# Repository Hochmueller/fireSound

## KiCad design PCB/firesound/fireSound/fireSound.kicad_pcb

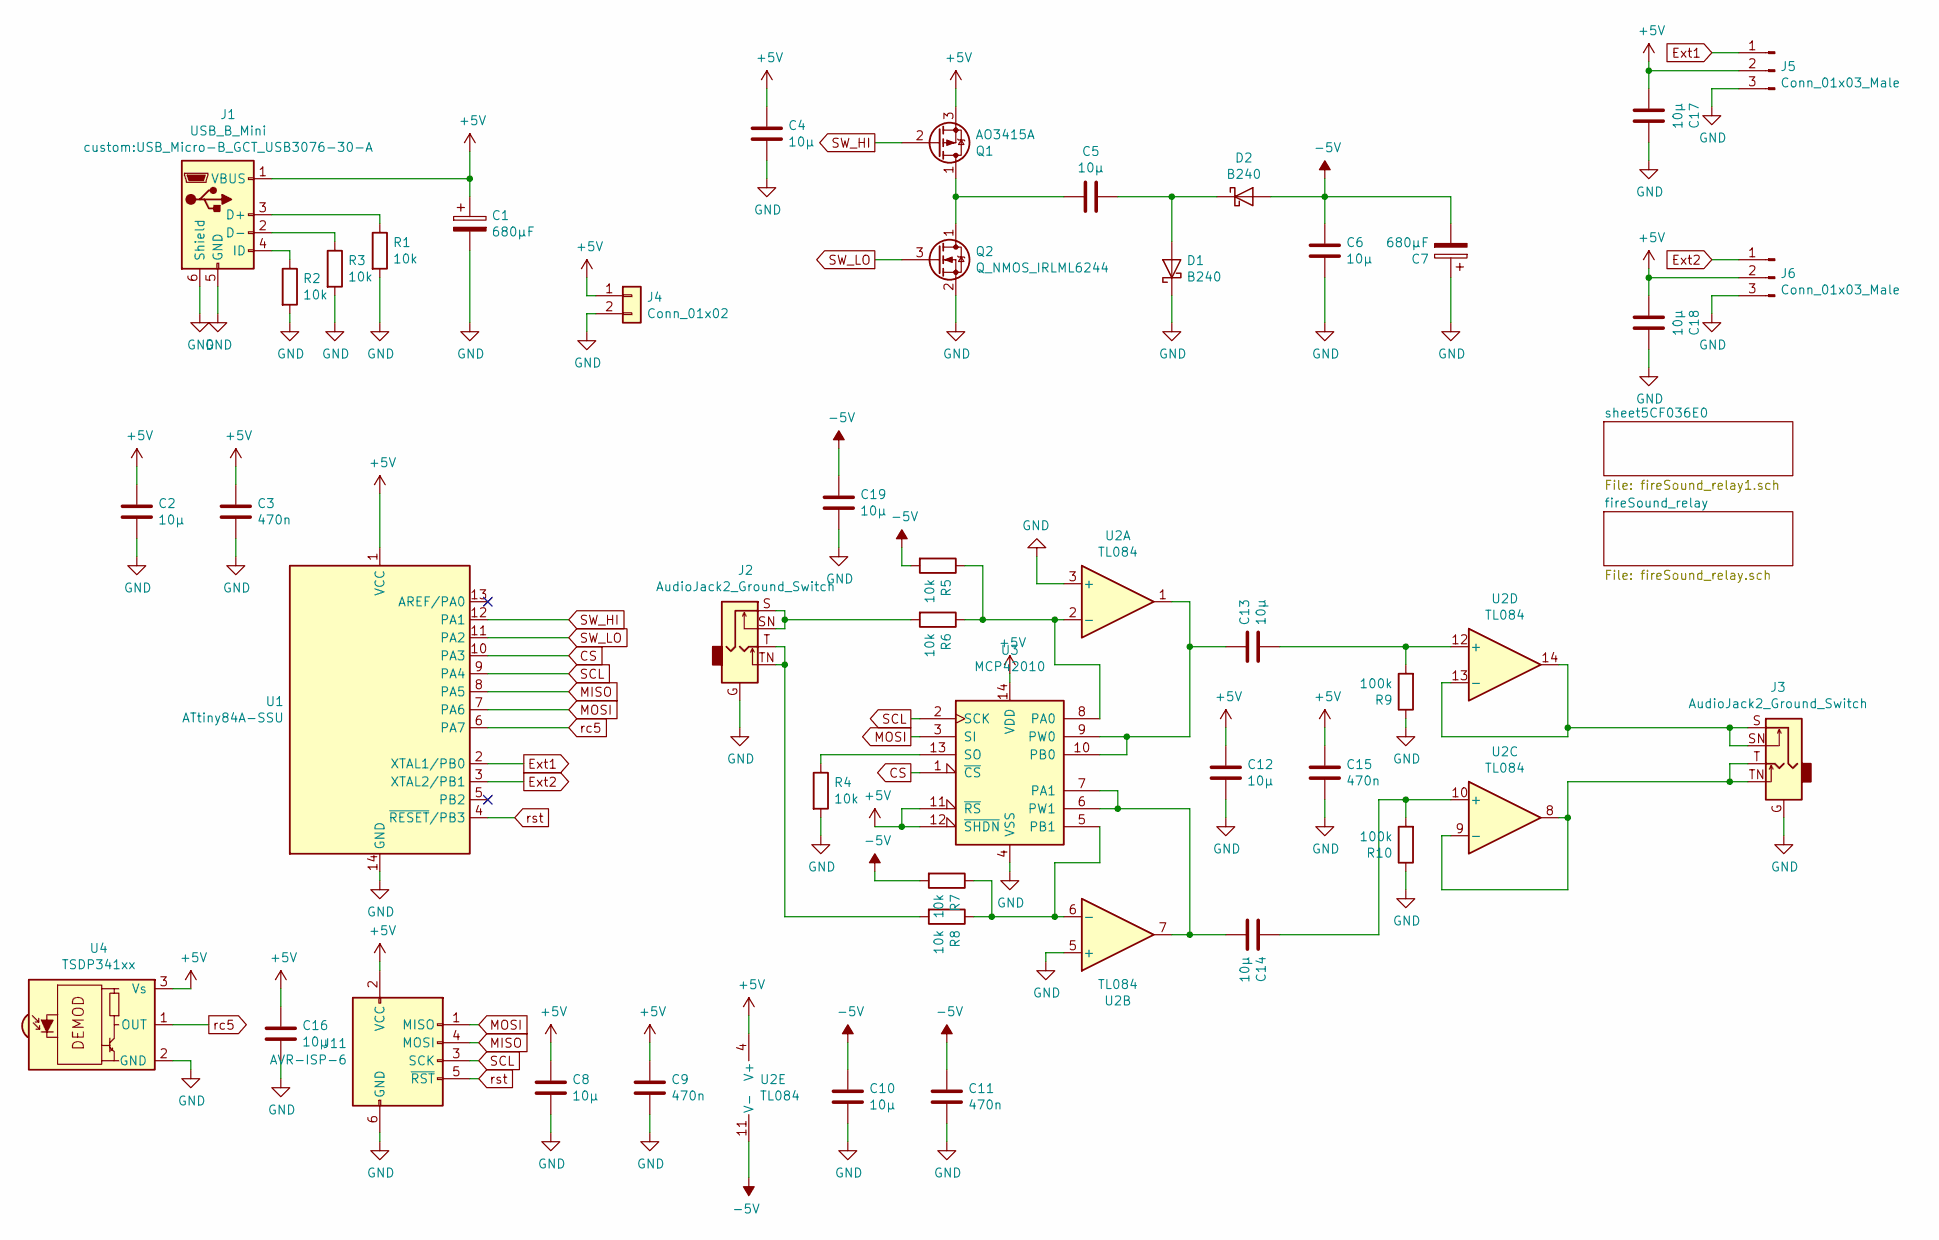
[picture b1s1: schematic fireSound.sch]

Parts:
C1, C7: 680µF; C_2816_7142Metric_Pad3.20x4.45mm_HandSolder
C2, C4, C5, C6, C8, C10, C12, C13, C14, C16, C17, C18, C19: 10µ; C_0603_1608Metric_Pad1.05x0.95mm_HandSolder
C3, C9, C11, C15: 470n; C_0603_1608Metric_Pad1.05x0.95mm_HandSolder
D1, D2: B240; D_SMB
J1: USB_B_Mini; USB_Micro-B_GCT_USB3076-30-A
J2, J3: AudioJack2_Ground_Switch; Jack_3.5mm_Horizontal
J4: Conn_01x02; PinHeader_1x02_P2.54mm_Vertical
J5, J6: Conn_01x03_Male; JST_PH_S3B-PH-K_1x03_P2.00mm_Horizontal
J11: AVR-ISP-6; PinHeader_2x03_P2.54mm_Vertical
Q1: AO3415A; AO3415A_SOT-23
Q2: Q_NMOS_IRLML6244; IRLML6244_SOT-23 - Kopie
R1, R2, R3, R4, R5, R6, R7, R8: 10k; R_0603_1608Metric_Pad1.05x0.95mm_HandSolder
R9, R10: 100k; R_0603_1608Metric_Pad1.05x0.95mm_HandSolder
U1: ATtiny84A-SSU; SOIC-14_3.9x8.7mm_P1.27mm
U2: TL084; SOIC-14_3.9x8.7mm_P1.27mm
U3: MCP42010; SOIC-14_3.9x8.7mm_P1.27mm
U4: TSDP341xx; Vishay_MOLD-3Pin

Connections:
+5V: C1.1, C2.1, C3.1, C4.1, C8.1, C9.1, C12.1, C15.1, C16.1, C17.2, C18.2, J1.1 (VBUS), J4.1, J5.2, J6.2, J11.2 (VCC), Q1.3 (S), U1.1 (VCC), U2.4 (V+), U3.11 (~RS), U3.12 (~SHDN), U3.14 (VDD), U4.3 (Vs)
-5V: C6.2, C7.2, C10.1, C11.1, C19.1, D2.2 (A), R5.2, R7.2, U2.11 (V-)
CS: U1.10 (PA3), U3.1 (~CS)
Ext1: J5.1, U1.2 (XTAL1/PB0)
Ext2: J6.1, U1.3 (XTAL2/PB1)
GND: C1.2, C2.2, C3.2, C4.2, C6.1, C7.1, C8.2, C9.2, C10.2, C11.2, C12.2, C15.2, C16.2, C17.1, C18.1, C19.2, D1.1 (K), J1.5 (GND), J1.6 (Shield), J2.G, J3.G, J4.2, J5.3, J6.3, J11.6 (GND), Q2.2 (S), R1.2, R2.2, R3.2, R4.2, R9.1, R10.1, U1.14 (GND), U2.3 (+), U2.5 (+), U3.4 (VSS), U4.2 (GND)
MISO: J11.4 (MOSI), U1.8 (PA5)
MOSI: J11.1 (MISO), U1.7 (PA6), U3.3 (SI)
unnamed: C5.1, D1.2 (A), D2.1 (K)
unnamed: C5.2, Q1.1 (D), Q2.1 (D)
unnamed: C13.1, U2.1, U3.9 (PW0), U3.10 (PB0)
unnamed: C13.2, R9.2, U2.12 (+)
unnamed: C14.1, R10.2, U2.10 (+)
unnamed: C14.2, U2.7, U3.6 (PW1), U3.7 (PA1)
unnamed: J1.2 (D-), R3.1
unnamed: J1.3 (D+), R1.1
unnamed: J1.4 (ID), R2.1
unnamed: J2.S, J2.SN, R6.2
unnamed: J2.T, J2.TN, R8.2
unnamed: J3.S, J3.SN, U2.13 (-), U2.14
unnamed: J3.T, J3.TN, U2.8, U2.9 (-)
unnamed: R4.1, U3.13 (SO)
unnamed: R5.1, R6.1, U2.2 (-), U3.8 (PA0)
unnamed: R7.1, R8.1, U2.6 (-), U3.5 (PB1)
SCL: J11.3 (SCK), U1.9 (PA4), U3.2 (SCK)
SW_HI: Q1.2 (G), U1.12 (PA1)
SW_LO: Q2.3 (G), U1.11 (PA2)
rc5: U1.6 (PA7), U4.1 (OUT)
rst: J11.5 (~RST), U1.4 (~RESET~/PB3)

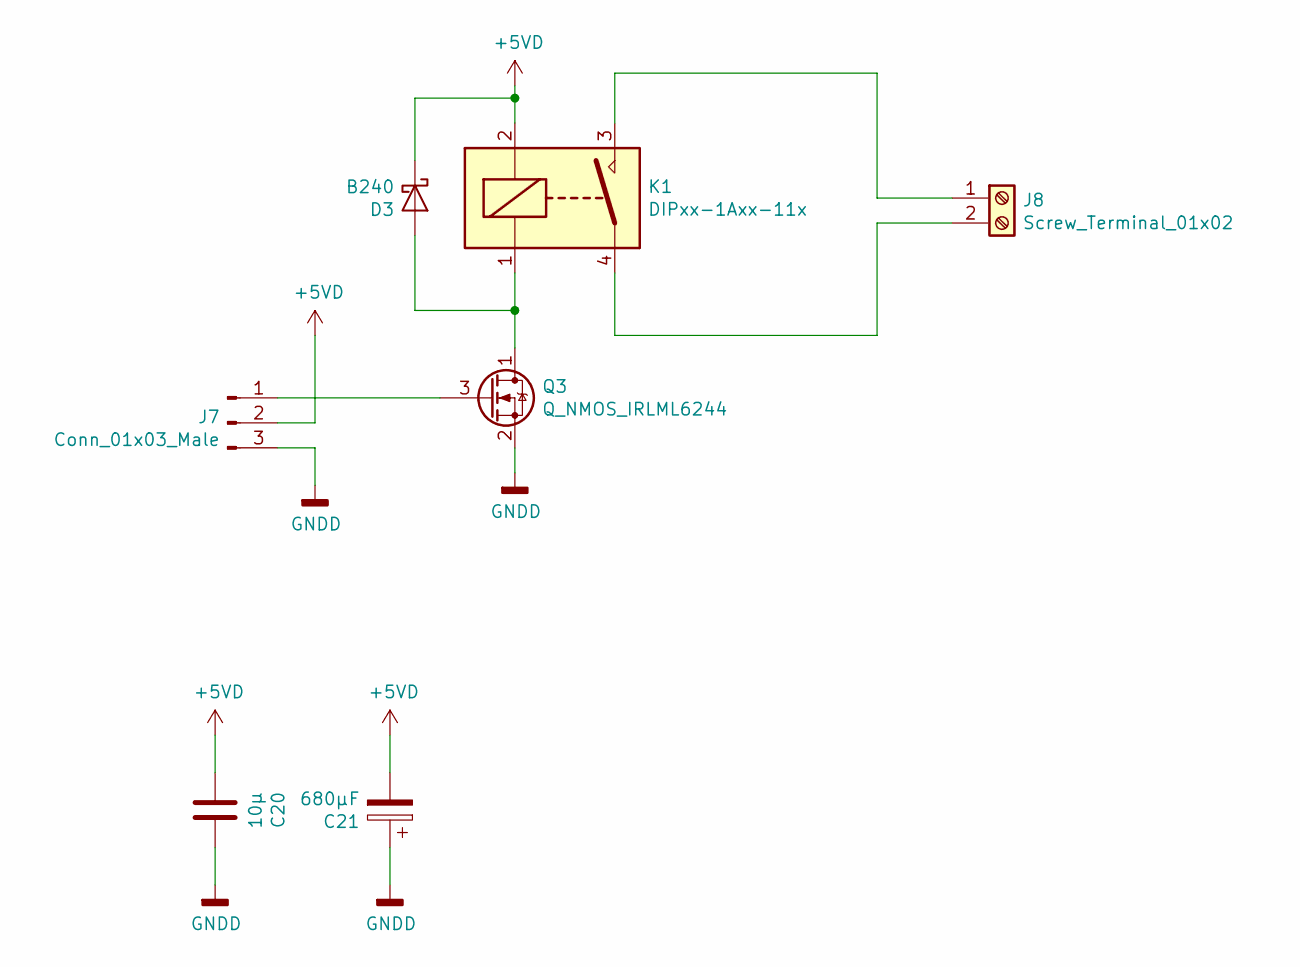
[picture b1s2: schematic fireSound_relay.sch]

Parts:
C20: 10µ; C_0603_1608Metric_Pad1.05x0.95mm_HandSolder
C21: 680µF; C_2816_7142Metric_Pad3.20x4.45mm_HandSolder
D3: B240; D_SMB
J7: Conn_01x03_Male; JST_PH_S3B-PH-K_1x03_P2.00mm_Horizontal
J8: Screw_Terminal_01x02; TerminalBlock_bornier-2_P5.08mm
K1: DIPxx-1Axx-11x; JV_05_relai
Q3: Q_NMOS_IRLML6244; IRLML6244_SOT-23 - Kopie

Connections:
+5VD: C20.2, C21.2, D3.1 (K), J7.2, K1.2
GNDD: C20.1, C21.1, J7.3, Q3.2 (S)
unnamed: D3.2 (A), K1.1, Q3.1 (D)
unnamed: J7.1, Q3.3 (G)
unnamed: J8.1, K1.3
unnamed: J8.2, K1.4

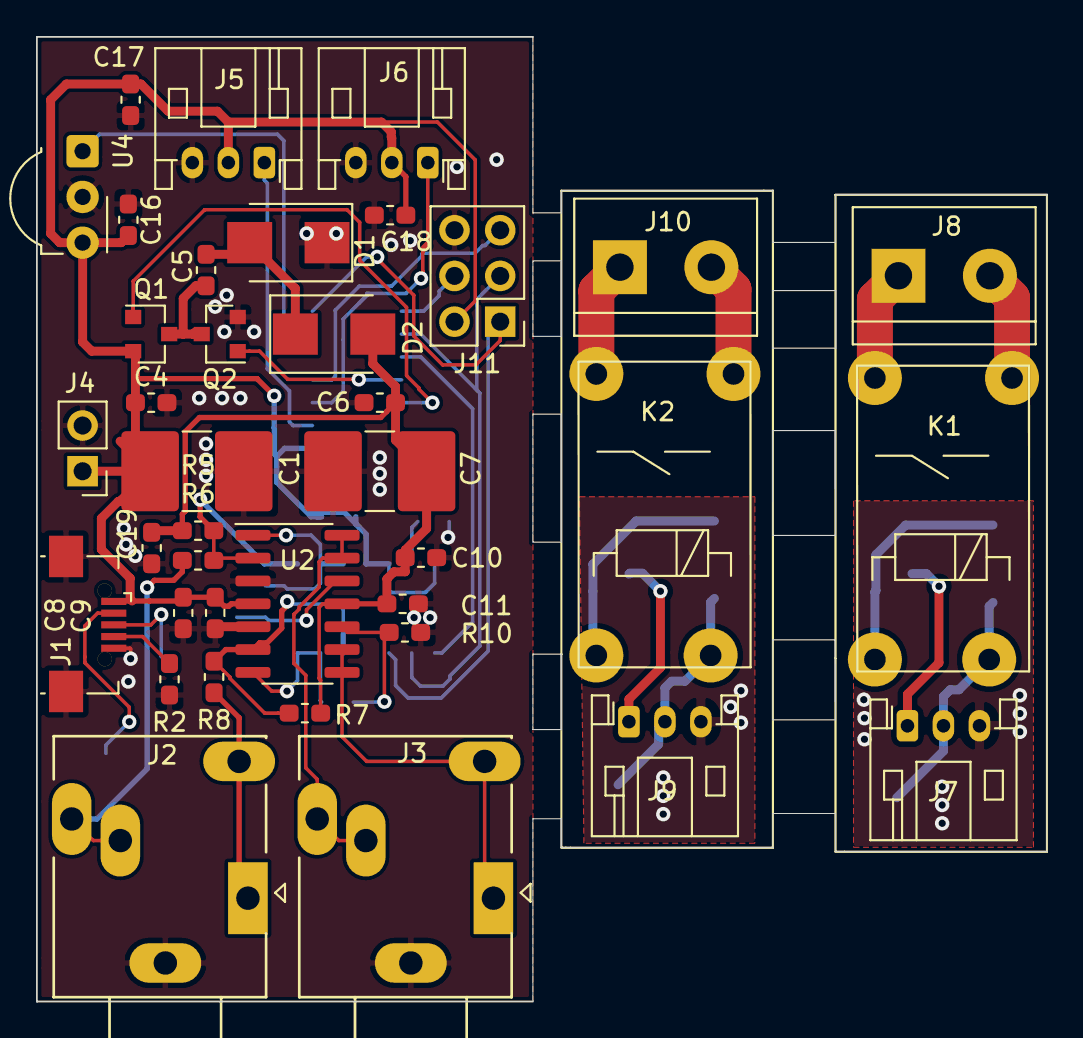
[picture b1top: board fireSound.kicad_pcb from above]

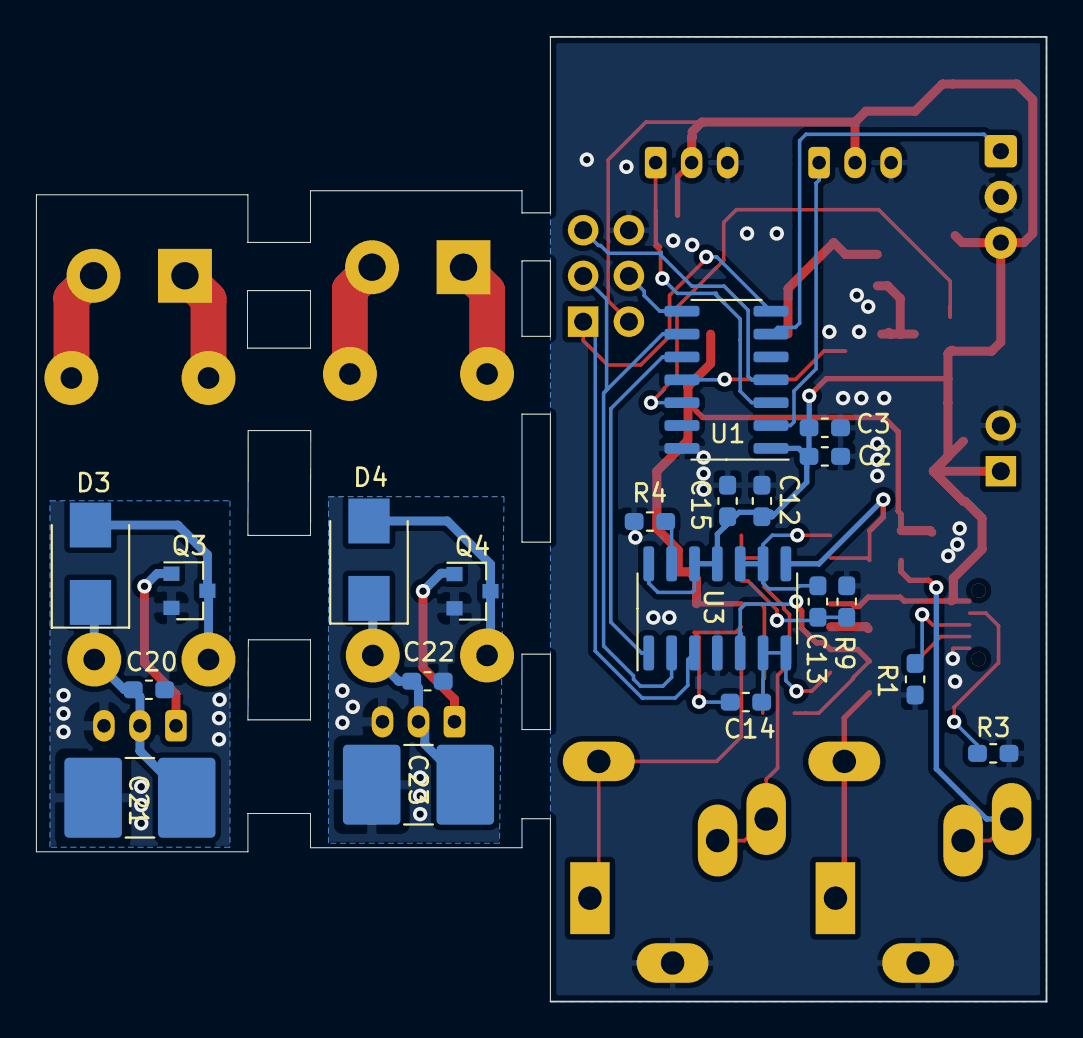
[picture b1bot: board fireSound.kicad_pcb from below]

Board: 2 copper layers, 56.1 x 53.6 mm, 58 parts (20 on the bottom side), 41 nets.

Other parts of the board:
C22: 10µ; C_0603_1608Metric_Pad1.05x0.95mm_HandSolder
C23: 680µF; C_2816_7142Metric_Pad3.20x4.45mm_HandSolder
D4: B240; D_SMB
J9: Conn_01x03_Male; JST_PH_S3B-PH-K_1x03_P2.00mm_Horizontal
J10: Screw_Terminal_01x02; TerminalBlock_bornier-2_P5.08mm
K2: DIPxx-1Axx-11x; JV_05_relai
Q4: Q_NMOS_IRLML6244; IRLML6244_SOT-23 - Kopie

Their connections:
+5VA: C22.2, C23.2, D4.1, J9.2, K2.2
GNDA: C22.1, C23.1, J9.3, Q4.2
unnamed: D4.2, K2.1, Q4.1
unnamed: J9.1, Q4.3
unnamed: J10.1, K2.3
unnamed: J10.2, K2.4

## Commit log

2019-07-03 Add LTSpace simulation
2019-07-03 add KiCad project with BOM
2019-07-03 rearange file structure
